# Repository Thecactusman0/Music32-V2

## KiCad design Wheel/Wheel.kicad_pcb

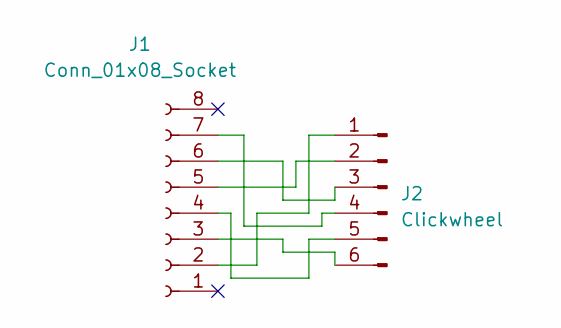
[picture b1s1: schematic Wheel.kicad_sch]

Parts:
J1: Conn_01x08_Socket; 0.5-8P CTXJ-H2.0 119
J2: Clickwheel; clickwheel6

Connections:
unnamed: J1.2, J2.1
unnamed: J1.3, J2.6
unnamed: J1.4, J2.5
unnamed: J1.5, J2.2
unnamed: J1.6, J2.3
unnamed: J1.7, J2.4

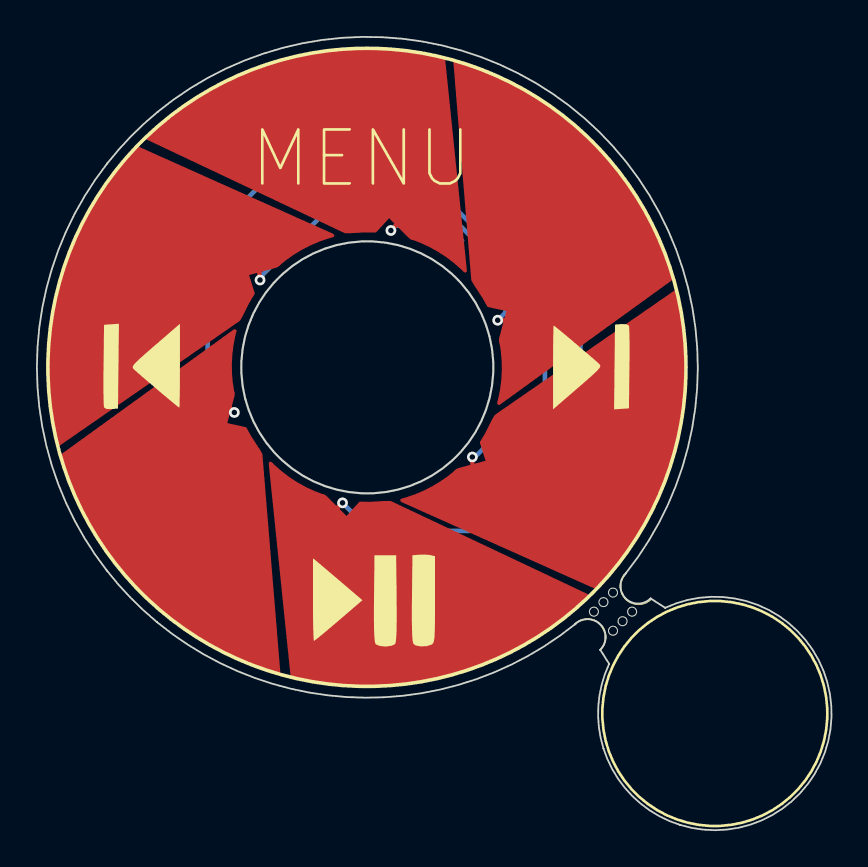
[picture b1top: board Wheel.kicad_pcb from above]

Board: 2 copper layers, 44.1 x 44.1 mm, 3 parts (1 on the bottom side), 6 nets.

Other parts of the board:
mouse-bite-2mm-slot: VAL**; mouse-bite-2mm-slot

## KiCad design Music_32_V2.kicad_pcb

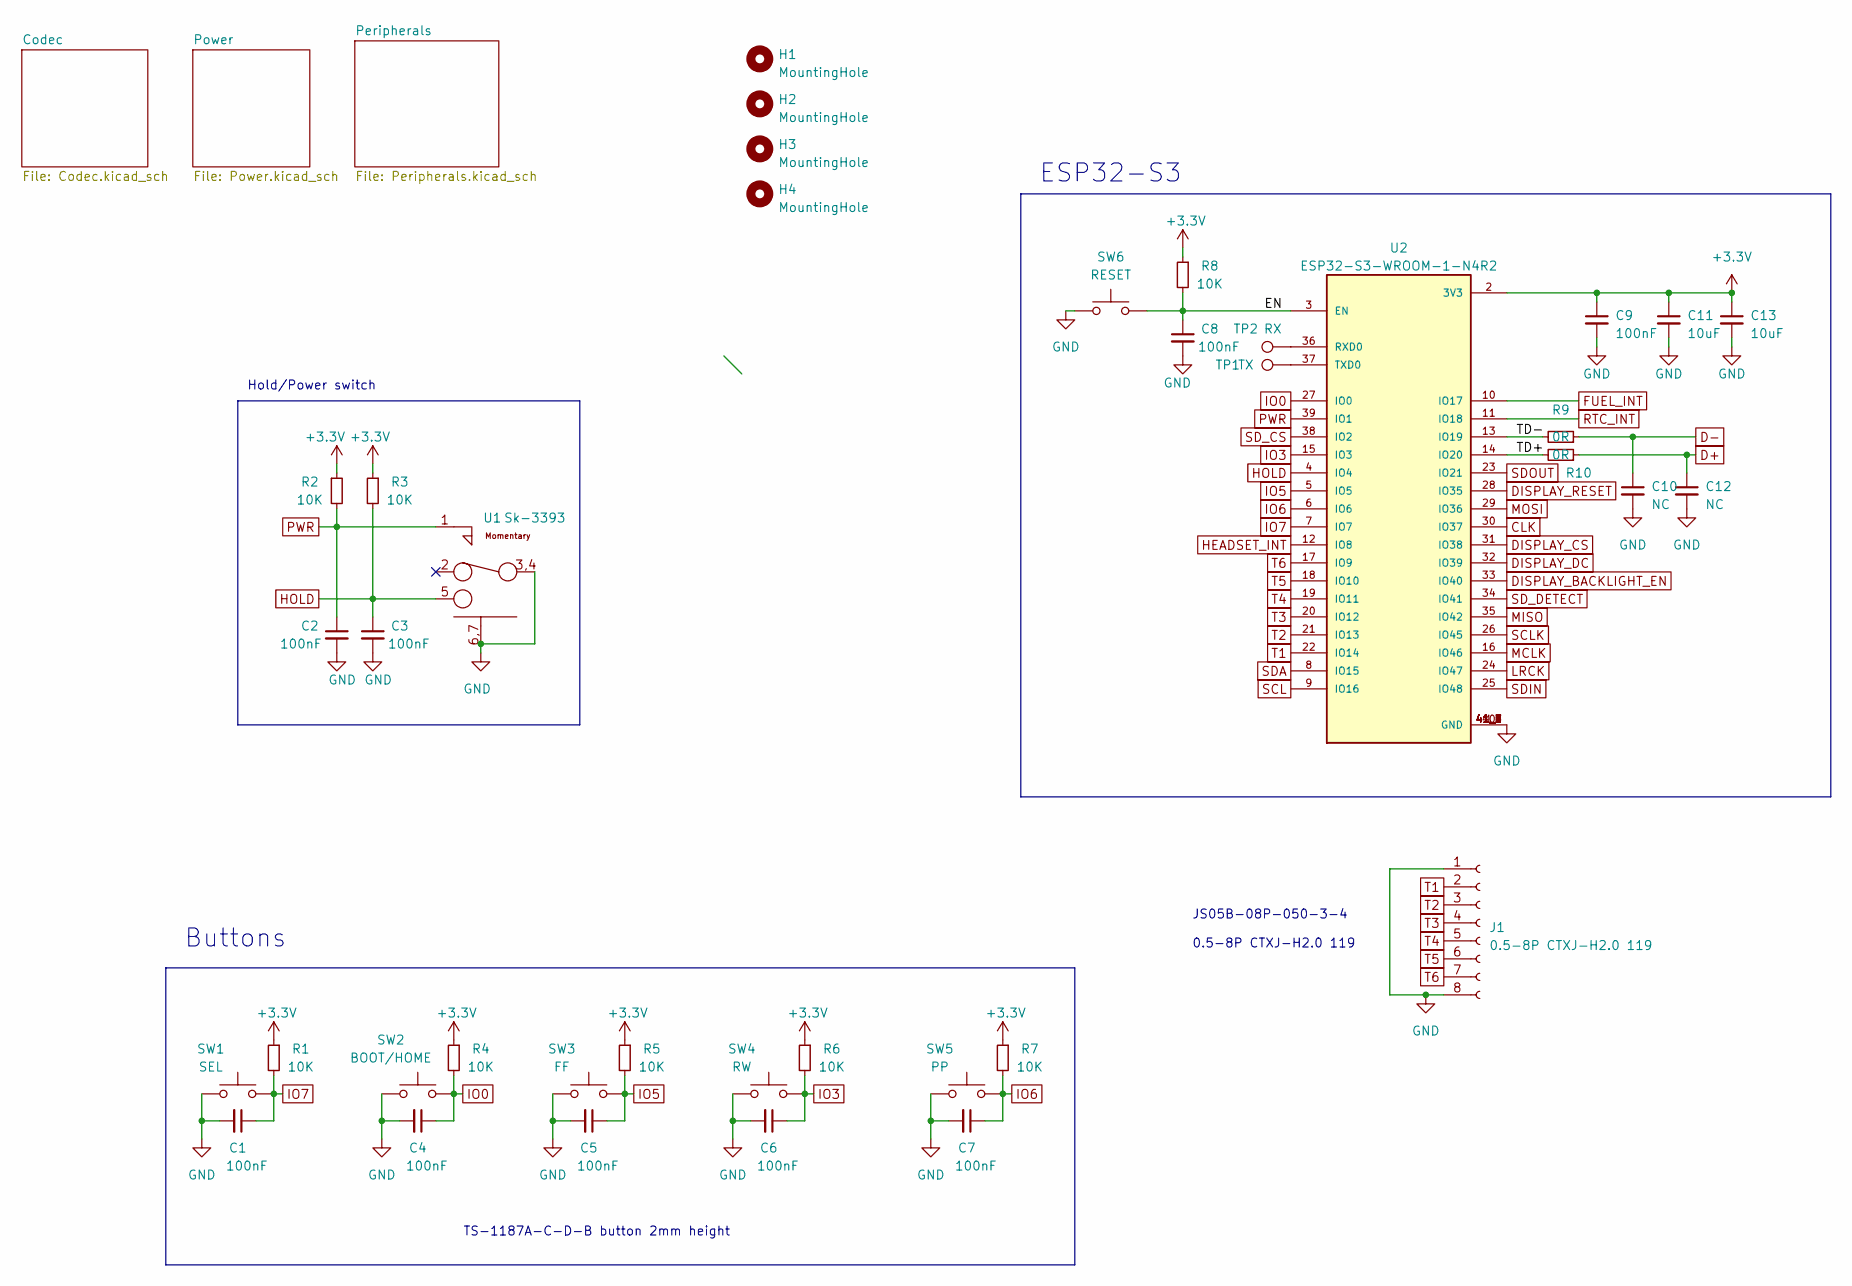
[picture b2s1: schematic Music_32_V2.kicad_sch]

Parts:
C1, C2, C3, C4, C5, C6, C7, C8, C9: 100nF; C_0402_1005Metric
C10, C12: NC; C_0402_1005Metric
C11, C13: 10uF; C_0603_1608Metric
H1, H2, H3, H4: MountingHole; MountingHole_2.2mm_M2
J1: 0.5-8P CTXJ-H2.0 119
R1, R2, R3, R4, R5, R6, R7, R8: 10K; R_0402_1005Metric
R9, R10: 0R; R_0402_1005Metric
SW1: SEL; SW_Push_1P1T_XKB_TS-1187A
SW2: BOOT/HOME; SW_Push_1P1T_XKB_TS-1187A
SW3: FF; SW_Push_1P1T_XKB_TS-1187A
SW4: RW; SW_Push_1P1T_XKB_TS-1187A
SW5: PP; SW_Push_1P1T_XKB_TS-1187A
SW6: RESET; SW_Push_1P1T_XKB_TS-1187A
TP1: TX; TestPoint_Pad_D3.0mm
TP2: RX; TestPoint_Pad_D3.0mm
U1: Sk-3393; SK-3393M-G1
U2: ESP32-S3-WROOM-1-N4R2; XCVR_ESP32-S3-WROOM-1-N4R2; PARTREV v1.0

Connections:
+3.3V: C9.1, C11.1, C13.1, R1.1, R2.1, R3.1, R4.1, R5.1, R6.1, R7.1, R8.1, U2.2 (3V3); also elsewhere on the board
/EN: C8.1, R8.2, SW6.1, U2.3 (EN)
/TD+: R10.2, U2.14 (IO20)
/TD-: R9.2, U2.13 (IO19)
CLK: U2.30 (IO37); also elsewhere on the board
D+: C12.1, R10.1; also elsewhere on the board
D-: C10.1, R9.1; also elsewhere on the board
DISPLAY_BACKLIGHT_EN: U2.33 (IO40); also elsewhere on the board
DISPLAY_CS: U2.31 (IO38); also elsewhere on the board
DISPLAY_DC: U2.32 (IO39); also elsewhere on the board
DISPLAY_RESET: U2.28 (IO35); also elsewhere on the board
FUEL_INT: U2.10 (IO17); also elsewhere on the board
GND: C1.2, C2.2, C3.2, C4.2, C5.2, C6.2, C7.2, C8.2, C9.2, C10.2, C11.2, C12.2, C13.2, J1.1, J1.8, SW1.2, SW2.2, SW3.2, SW4.2, SW5.2, SW6.2, U1.3,4, U1.6,7, U2.1 (GND), U2.40 (GND), U2.41_1 (GND), U2.41_2 (GND), U2.41_3 (GND), U2.41_4 (GND), U2.41_5 (GND), U2.41_6 (GND), U2.41_7 (GND), U2.41_8 (GND), U2.41_9 (GND); also elsewhere on the board
HEADSET_INT: U2.12 (IO8); also elsewhere on the board
HOLD: C3.1, R3.2, U1.5, U2.4 (IO4)
IO0: C4.1, R4.2, SW2.1, U2.27 (IO0)
IO3: C6.1, R6.2, SW4.1, U2.15 (IO3)
IO5: C5.1, R5.2, SW3.1, U2.5 (IO5)
IO6: C7.1, R7.2, SW5.1, U2.6 (IO6)
IO7: C1.1, R1.2, SW1.1, U2.7 (IO7)
LRCK: U2.24 (IO47); also elsewhere on the board
MCLK: U2.16 (IO46); also elsewhere on the board
MISO: U2.35 (IO42); also elsewhere on the board
MOSI: U2.29 (IO36); also elsewhere on the board
unnamed: TP1.1, U2.37 (TXD0)
PWR: C2.1, R2.2, U1.1, U2.39 (IO1)
RTC_INT: U2.11 (IO18); also elsewhere on the board
SCL: U2.9 (IO16); also elsewhere on the board
SCLK: U2.26 (IO45); also elsewhere on the board
SDA: U2.8 (IO15); also elsewhere on the board
SDIN: U2.25 (IO48); also elsewhere on the board
SDOUT: U2.23 (IO21); also elsewhere on the board
SD_CS: U2.38 (IO2); also elsewhere on the board
SD_DETECT: U2.34 (IO41); also elsewhere on the board
T1: J1.2, U2.22 (IO14)
T2: J1.3, U2.21 (IO13)
T3: J1.4, U2.20 (IO12)
T4: J1.5, U2.19 (IO11)
T5: J1.6, U2.18 (IO10)
T6: J1.7, U2.17 (IO9)

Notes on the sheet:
Hold/Power switch
ESP32-S3
JS05B-08P-050-3-4 0.5-8P CTXJ-H2.0 119
TS-1187A-C-D-B button 2mm height
Buttons

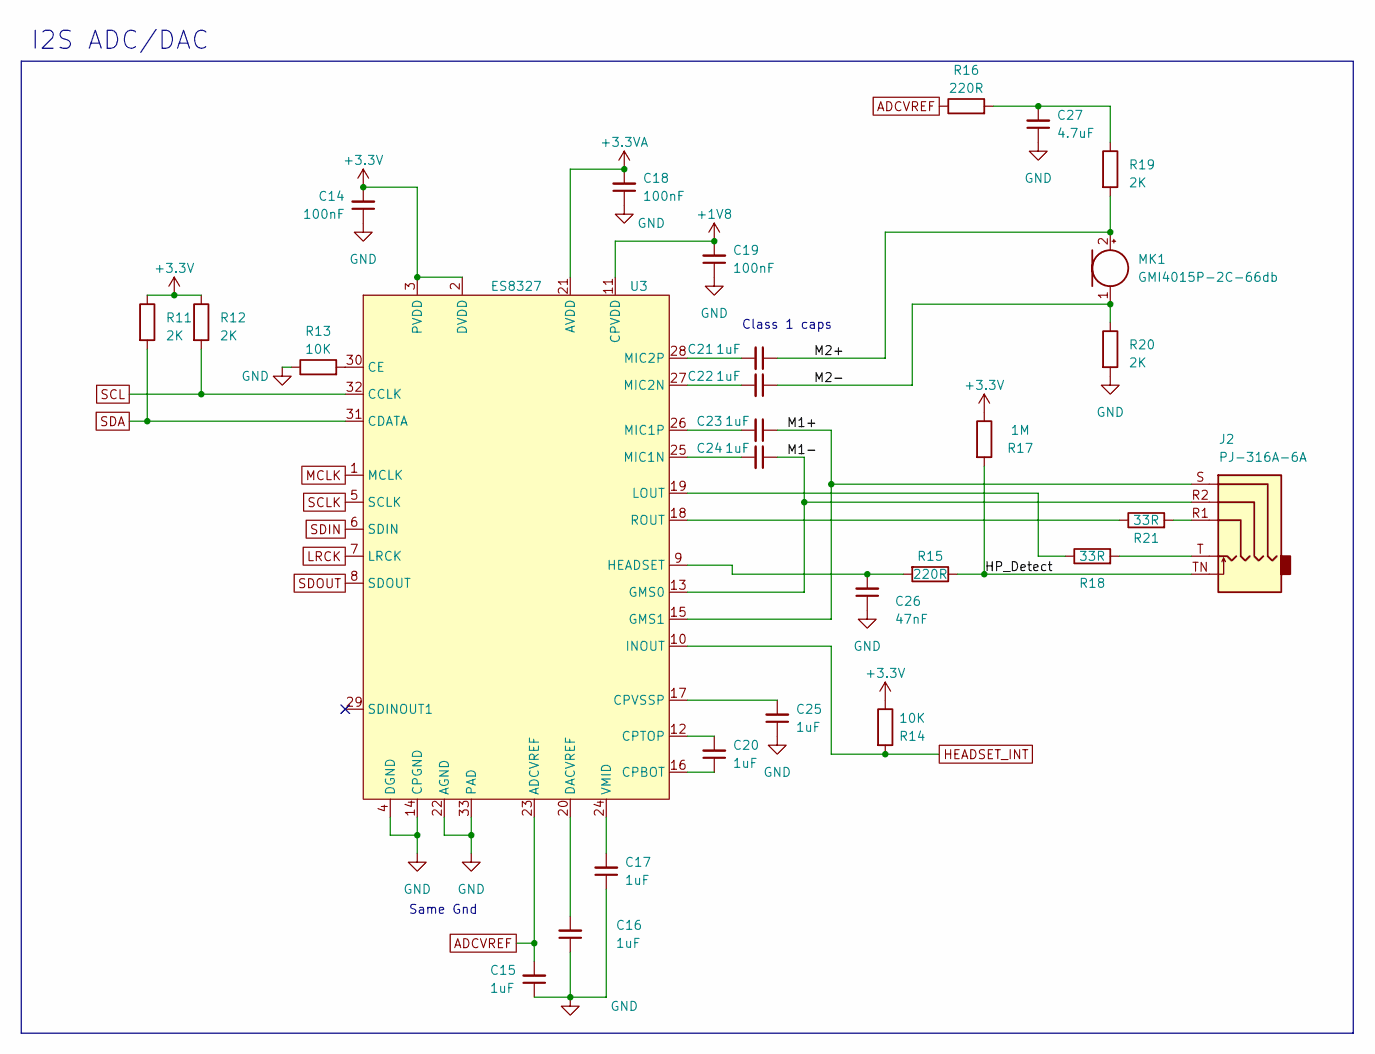
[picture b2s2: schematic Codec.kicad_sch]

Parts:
C14, C18, C19: 100nF; C_0402_1005Metric
C15, C16, C17, C20, C21, C22, C23, C24, C25: 1uF; C_0402_1005Metric
C26: 47nF; C_0402_1005Metric
C27: 4.7uF; C_0402_1005Metric
J2: PJ-316A-6A
MK1: GMI4015P-2C-66db
R11, R12, R19, R20: 2K; R_0402_1005Metric
R13, R14: 10K; R_0402_1005Metric
R15, R16: 220R; R_0402_1005Metric
R17: 1M; R_0402_1005Metric
R18, R21: 33R; R_0402_1005Metric
U3: ES8327; QFN-32-1EP_4x4mm_P0.4mm_EP2.9x2.9mm_ThermalVias

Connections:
+1V8: C19.2, U3.11 (CPVDD); also elsewhere on the board
+3.3V: C14.2, R11.1, R12.1, R14.1, R17.1, U3.2 (DVDD), U3.3 (PVDD); also elsewhere on the board
+3.3VA: C18.2, U3.21 (AVDD); also elsewhere on the board
/Codec/HP_Detect: J2.TN, R15.1, R17.2
/Codec/M1+: C23.1, J2.S, U3.15 (GMS1)
/Codec/M1-: C24.1, J2.R2, U3.13 (GMS0)
/Codec/M2+: C21.1, MK1.2 (+), R19.2
/Codec/M2-: C22.1, MK1.1 (-), R20.1
ADCVREF: C15.2, R16.1, U3.23 (ADCVREF)
GND: C14.1, C15.1, C16.1, C17.1, C18.1, C19.1, C25.1, C26.1, C27.1, R13.1, R20.2, U3.4 (DGND), U3.14 (CPGND), U3.22 (AGND), U3.33 (PAD); also elsewhere on the board
HEADSET_INT: R14.2, U3.10 (INOUT); also elsewhere on the board
LRCK: U3.7 (LRCK); also elsewhere on the board
MCLK: U3.1 (MCLK); also elsewhere on the board
unnamed: C27.2, R16.2, R19.1
unnamed: J2.R1, R21.2
unnamed: J2.T, R18.2
unnamed: R13.2, U3.30 (CE)
unnamed: C20.1, U3.16 (CPBOT)
unnamed: C20.2, U3.12 (CPTOP)
unnamed: C25.2, U3.17 (CPVSSP)
unnamed: C16.2, U3.20 (DACVREF)
unnamed: C26.2, R15.2, U3.9 (HEADSET)
unnamed: R18.1, U3.19 (LOUT)
unnamed: C24.2, U3.25 (MIC1N)
unnamed: C23.2, U3.26 (MIC1P)
unnamed: C22.2, U3.27 (MIC2N)
unnamed: C21.2, U3.28 (MIC2P)
unnamed: R21.1, U3.18 (ROUT)
unnamed: C17.2, U3.24 (VMID)
SCL: R12.2, U3.32 (CCLK); also elsewhere on the board
SCLK: U3.5 (SCLK); also elsewhere on the board
SDA: R11.2, U3.31 (CDATA); also elsewhere on the board
SDIN: U3.6 (SDIN); also elsewhere on the board
SDOUT: U3.8 (SDOUT); also elsewhere on the board

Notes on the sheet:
Same Gnd
I2S ADC/DAC
Class 1 caps

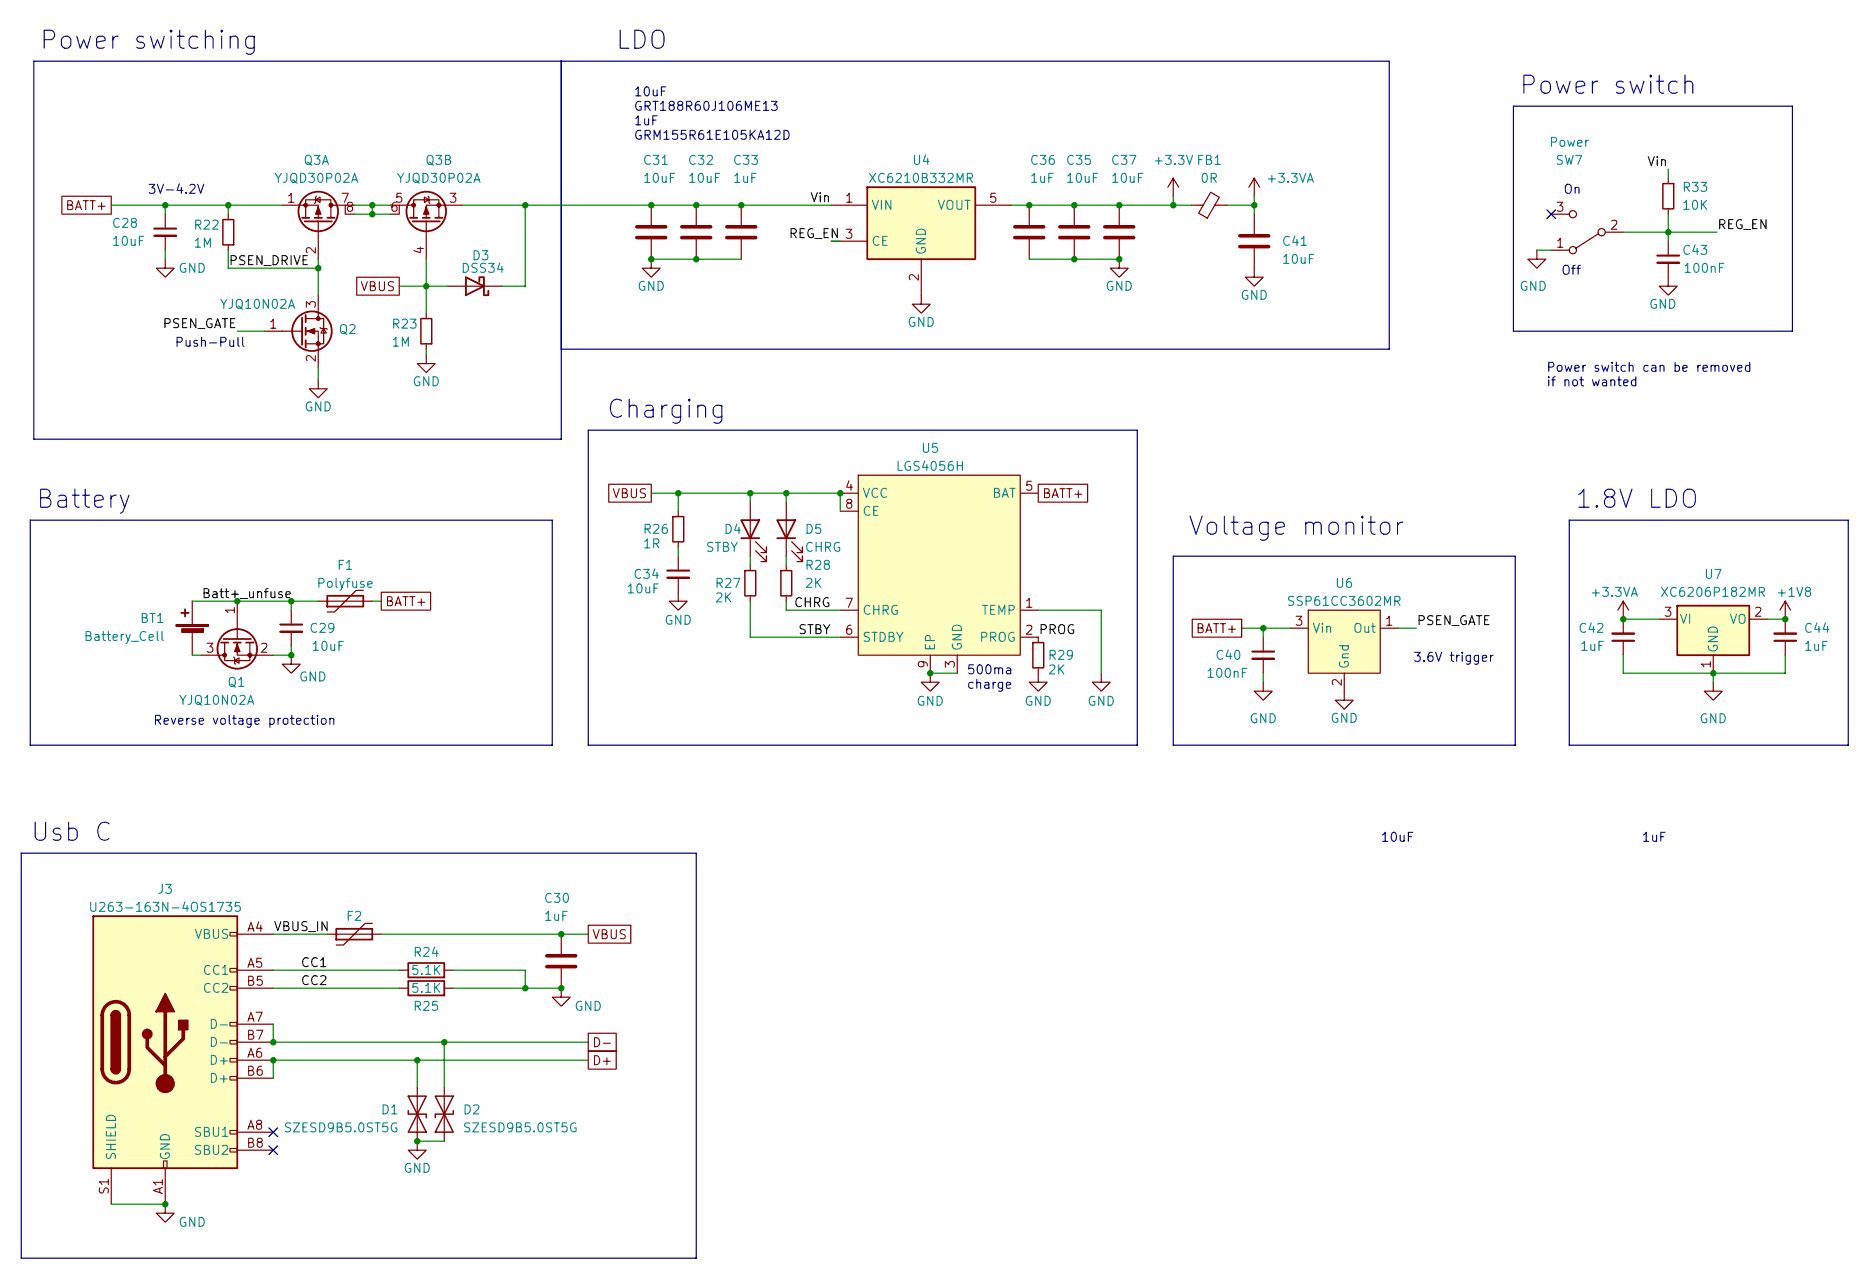
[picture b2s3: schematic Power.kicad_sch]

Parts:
BT1: Battery_Cell; JST_PH_S2B-PH-SM4-TB_1x02-1MP_P2.00mm_Horizontal
C28, C29: 10uF; C_0603_1608Metric; MPN 490-GRT155C80J105KE01JCT-ND
C30, C33, C36, C42, C44: 1uF; C_0402_1005Metric
C31, C32, C34, C35, C37, C41: 10uF; C_0603_1608Metric
C40: 100nF; C_0402_1005Metric; MPN_LCSC C41851
C43: 100nF; C_0402_1005Metric
D1, D2: SZESD9B5.0ST5G; D_SOD-923
D3: DSS34; D_SOD-123F; MPN_LCSC C2937163
D4: STBY; LED_0402_1005Metric
D5: CHRG; LED_0402_1005Metric
F1, F2: Polyfuse; Fuse_0603_1608Metric
FB1: 0R; R_0402_1005Metric
J3: U263-163N-4OS1735
Q1, Q2: YJQ10N02A
Q3: YJQD30P02A; YJQD30P02A_DFN3.3x3.3
R22, R23: 1M; R_0402_1005Metric; MPN_LCSC 1
R24, R25: 5.1K; R_0402_1005Metric
R26: 1R; R_0402_1005Metric
R27, R28, R29: 2K; R_0402_1005Metric
R33: 10K; R_0402_1005Metric
SW7: Power; SW_SPDT_PCM12
U4: XC6210B332MR; SOT-23-5
U5: LGS4056H; DFN-8-1EP_2x2mm_P0.5mm_EP0.9x1.6mm
U6: SSP61CC3602MR; SOT-23-3
U7: XC6206P182MR; SOT-23-3

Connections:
+1V8: C44.2, U7.2 (VO); also elsewhere on the board
+3.3V: C35.1, C36.1, C37.1, FB1.1, U4.5 (VOUT); also elsewhere on the board
+3.3VA: C41.1, C42.2, FB1.2, U7.3 (VI); also elsewhere on the board
/Power/Batt+_unfuse: BT1.2 (+), C29.1, F1.1, Q1.1 (G)
/Power/CC1: J3.A5 (CC1), R24.1
/Power/CC2: J3.B5 (CC2), R25.1
/Power/CHRG: R28.2, U5.7 (CHRG)
/Power/PROG: R29.1, U5.2 (PROG)
/Power/PSEN_DRIVE: Q2.3 (D), Q3.2 (G2), R22.1
/Power/PSEN_GATE: Q2.1 (G), U6.1 (Out)
/Power/REG_EN: C43.1, R33.2, SW7.2 (B), U4.3 (CE)
/Power/STBY: R27.2, U5.6 (STDBY)
/Power/VBUS_IN: F2.1, J3.A4 (VBUS), J3.A9 (VBUS), J3.B4 (VBUS), J3.B9 (VBUS)
/Power/Vin: C31.1, C32.1, C33.1, D3.1 (K), Q3.3 (S2), R33.1, U4.1 (VIN)
BATT+: C28.1, C40.1, F1.2, Q3.1 (S2), R22.2, U5.5 (BAT), U6.3 (Vin); also elsewhere on the board
D+: D1.2 (A2), J3.A6 (D+), J3.B6 (D+); also elsewhere on the board
D-: D2.2 (A2), J3.A7 (D-), J3.B7 (D-); also elsewhere on the board
GND: C28.2, C29.2, C30.2, C31.2, C32.2, C33.2, C34.2, C35.2, C36.2, C37.2, C40.2, C41.2, C42.1, C43.2, C44.1, D1.1 (A1), D2.1 (A1), J3.A1 (GND), J3.A12 (GND), J3.B1 (GND), J3.B12 (GND), J3.S1 (SHIELD), Q1.2 (S), Q2.2 (S), R23.1, R24.2, R25.2, R29.2, SW7.1 (A), U4.2 (GND), U5.1 (TEMP), U5.3 (GND), U5.9 (EP), U6.2 (Gnd), U7.1 (GND); also elsewhere on the board
unnamed: C34.1, R26.2
unnamed: D4.1 (K), R27.1
unnamed: D5.1 (K), R28.1
unnamed: BT1.1, Q1.3 (D)
unnamed: Q3.5 (D2), Q3.6 (D2), Q3.7 (D2), Q3.8 (D2)
VBUS: C30.1, D3.2 (A), D4.2 (A), D5.2 (A), F2.2, Q3.4 (G2), R23.2, R26.1, U5.4 (VCC), U5.8 (CE)

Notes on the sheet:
Battery
Reverse voltage protection
LDO
3.6V trigger
Power switching
Off
10uF
1uF
10uF GRT188R60J106ME13 1uF GRM155R61E105KA12D
Usb C
Push-Pull
Power switch
Voltage monitor
3V-4.2V
Charging
1.8V LDO
500ma charge
Power switch can be removed if not wanted

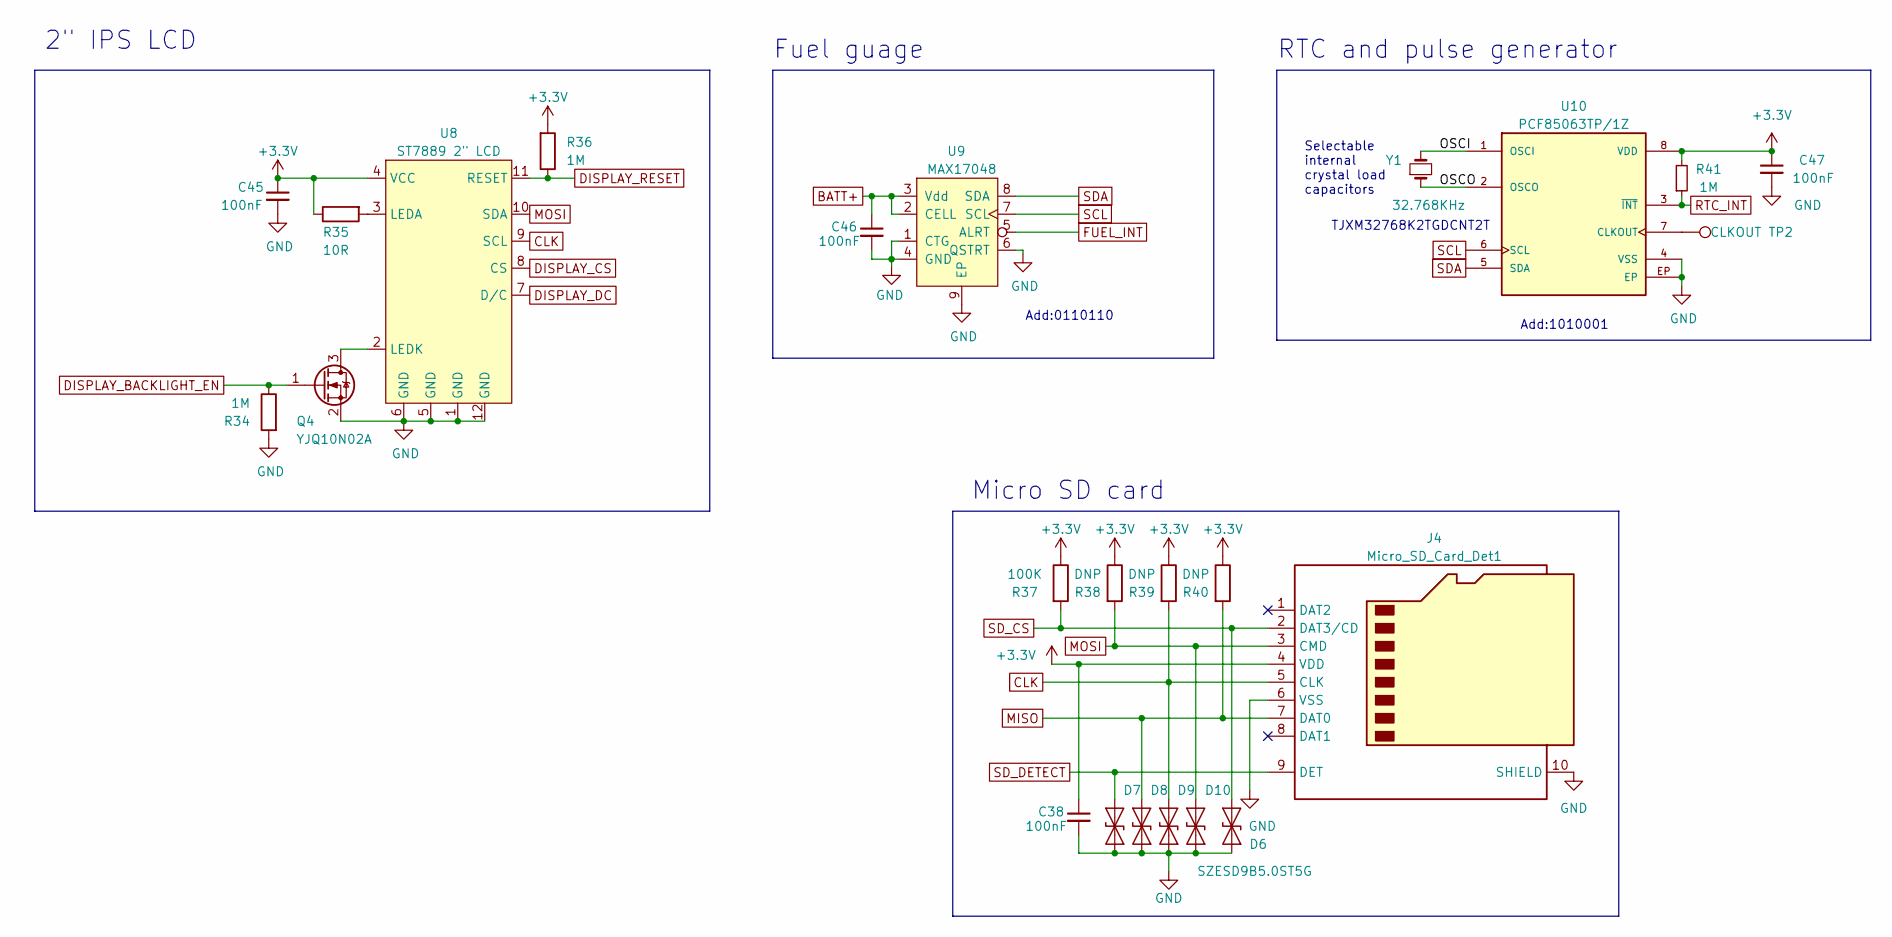
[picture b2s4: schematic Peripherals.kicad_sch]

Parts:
C38, C46: 100nF; C_0402_1005Metric; MPN 490-GRT155C80J105KE01JCT-ND
C45, C47: 100nF; C_0402_1005Metric
D6, D7, D8, D9, D10: SZESD9B5.0ST5G; D_SOD-923
J4: Micro_SD_Card_Det1; MOLEX_503398-1892
Q4: YJQ10N02A
R34, R36, R41: 1M; R_0402_1005Metric
R35: 10R; R_0402_1005Metric
R37: 100K; R_0402_1005Metric
R38, R39, R40: DNP; R_0402_1005Metric
TP2: CLKOUT; TestPoint_Pad_D3.0mm
U8: ST7889 2" LCD; TFT020-2_same_side
U9: MAX17048; DFN-8-1EP_2x2mm_P0.5mm_EP0.8x1.6mm
U10: PCF85063TP/1Z; PCF85063TP_1Z; MPN PCF85063TP/1Z; DIGIKEY_PARTNO 568-10236-1-ND
Y1: 32.768KHz; Crystal_SMD_2012-2Pin_2.0x1.2mm

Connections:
+3.3V: C38.1, C45.1, C47.1, J4.4 (VDD), R35.1, R36.2, R37.1, R38.1, R39.1, R40.1, R41.2, U8.4 (VCC), U10.8 (VDD); also elsewhere on the board
/Peripherals/OSCI: U10.1 (OSCI), Y1.2
/Peripherals/OSCO: U10.2 (OSCO), Y1.1
BATT+: C46.1, U9.2 (CELL), U9.3 (Vdd); also elsewhere on the board
CLK: D8.2 (A2), J4.5 (CLK), R39.2, U8.9 (SCL); also elsewhere on the board
DISPLAY_BACKLIGHT_EN: Q4.1 (G), R34.1; also elsewhere on the board
DISPLAY_CS: U8.8 (CS); also elsewhere on the board
DISPLAY_DC: U8.7 (D/C); also elsewhere on the board
DISPLAY_RESET: R36.1, U8.11 (RESET); also elsewhere on the board
FUEL_INT: U9.5 (ALRT); also elsewhere on the board
GND: C38.2, C45.2, C46.2, C47.2, D6.1 (A1), D7.1 (A1), D8.1 (A1), D9.1 (A1), D10.1 (A1), J4.6 (VSS), J4.10 (SHIELD), Q4.2 (S), R34.2, U8.1 (GND), U8.5 (GND), U8.6 (GND), U8.12 (GND), U9.1 (CTG), U9.4 (GND), U9.6 (QSTRT), U9.9 (EP), U10.4 (VSS), U10.EP; also elsewhere on the board
MISO: D7.2 (A2), J4.7 (DAT0), R40.2; also elsewhere on the board
MOSI: D9.2 (A2), J4.3 (CMD), R38.2, U8.10 (SDA); also elsewhere on the board
unnamed: Q4.3 (D), U8.2 (LEDK)
unnamed: R35.2, U8.3 (LEDA)
RTC_INT: R41.1, U10.3 (~INT); also elsewhere on the board
SCL: U9.7 (SCL), U10.6 (SCL); also elsewhere on the board
SDA: U9.8 (SDA), U10.5 (SDA); also elsewhere on the board
SD_CS: D10.2 (A2), J4.2 (DAT3/CD), R37.2; also elsewhere on the board
SD_DETECT: D6.2 (A2), J4.9 (DET); also elsewhere on the board

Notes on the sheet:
Selectable internal crystal load capacitors
Micro SD card
Fuel guage
Add:1010001
Add:0110110
RTC and pulse generator
2" IPS LCD
TJXM32768K2TGDCNT2T

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
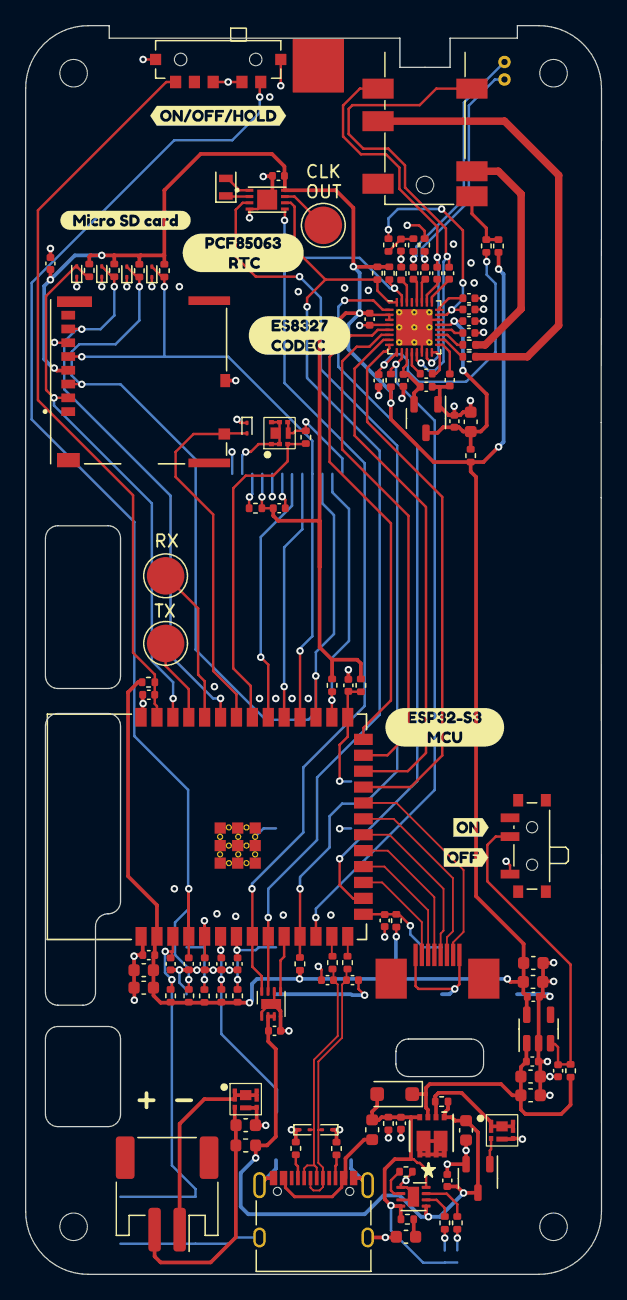
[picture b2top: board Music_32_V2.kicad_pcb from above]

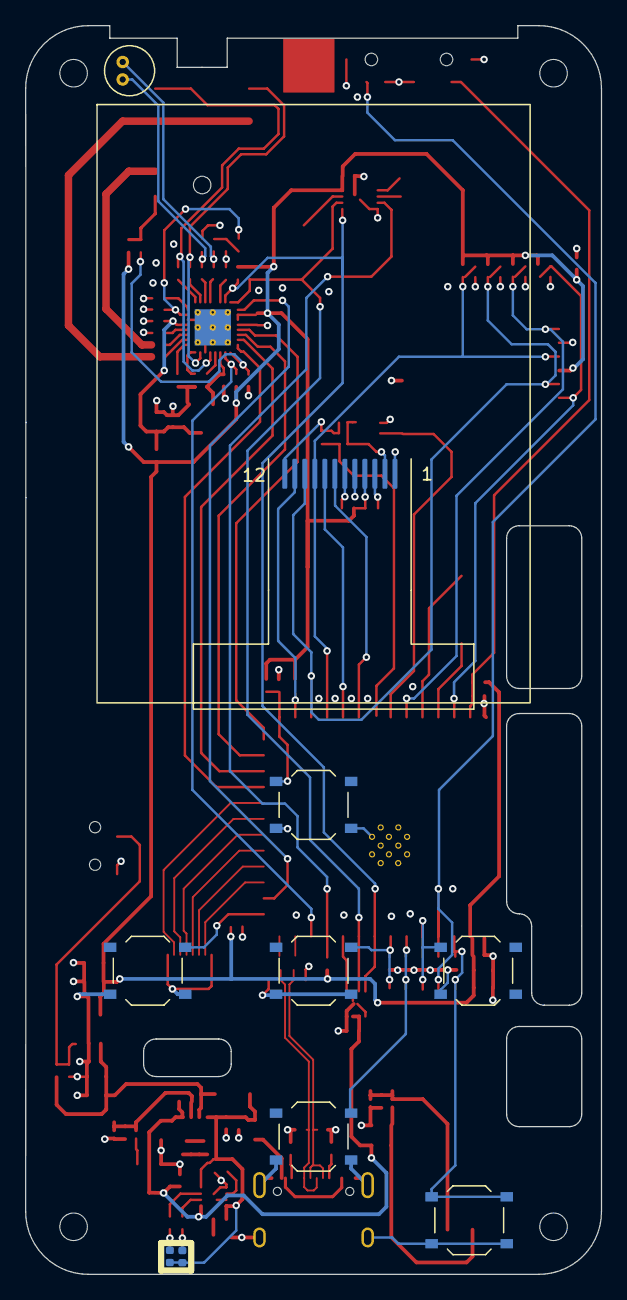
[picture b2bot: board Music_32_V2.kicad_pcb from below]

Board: 4 copper layers, 46.0 x 99.8 mm, 139 parts (10 on the bottom side), 88 nets.

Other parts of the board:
TP3: CLKOUT; TestPoint_Pad_D3.0mm
kibuzzard-64D61D91: G***; kibuzzard-64D61D91
kibuzzard-64D61DB7: G***; kibuzzard-64D61DB7
kibuzzard-64D61E16: G***; kibuzzard-64D61E16
kibuzzard-64D61E82: G***; kibuzzard-64D61E82
kibuzzard-64D61F3E: G***; kibuzzard-64D61F3E
kibuzzard-64D61F46: G***; kibuzzard-64D61F46
kibuzzard-64D61F96: G***; kibuzzard-64D61F96

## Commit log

2023-08-11 Stuff
2023-08-11 pdf schematic
2023-08-14 Did some things
2023-08-23 Removed slashes from filenames
